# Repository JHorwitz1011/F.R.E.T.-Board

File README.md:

# F.R.E.T.-Board

## Fall '23 Senior Project

Jim Horwitz, Julia Brubach, Peter Buglewicz

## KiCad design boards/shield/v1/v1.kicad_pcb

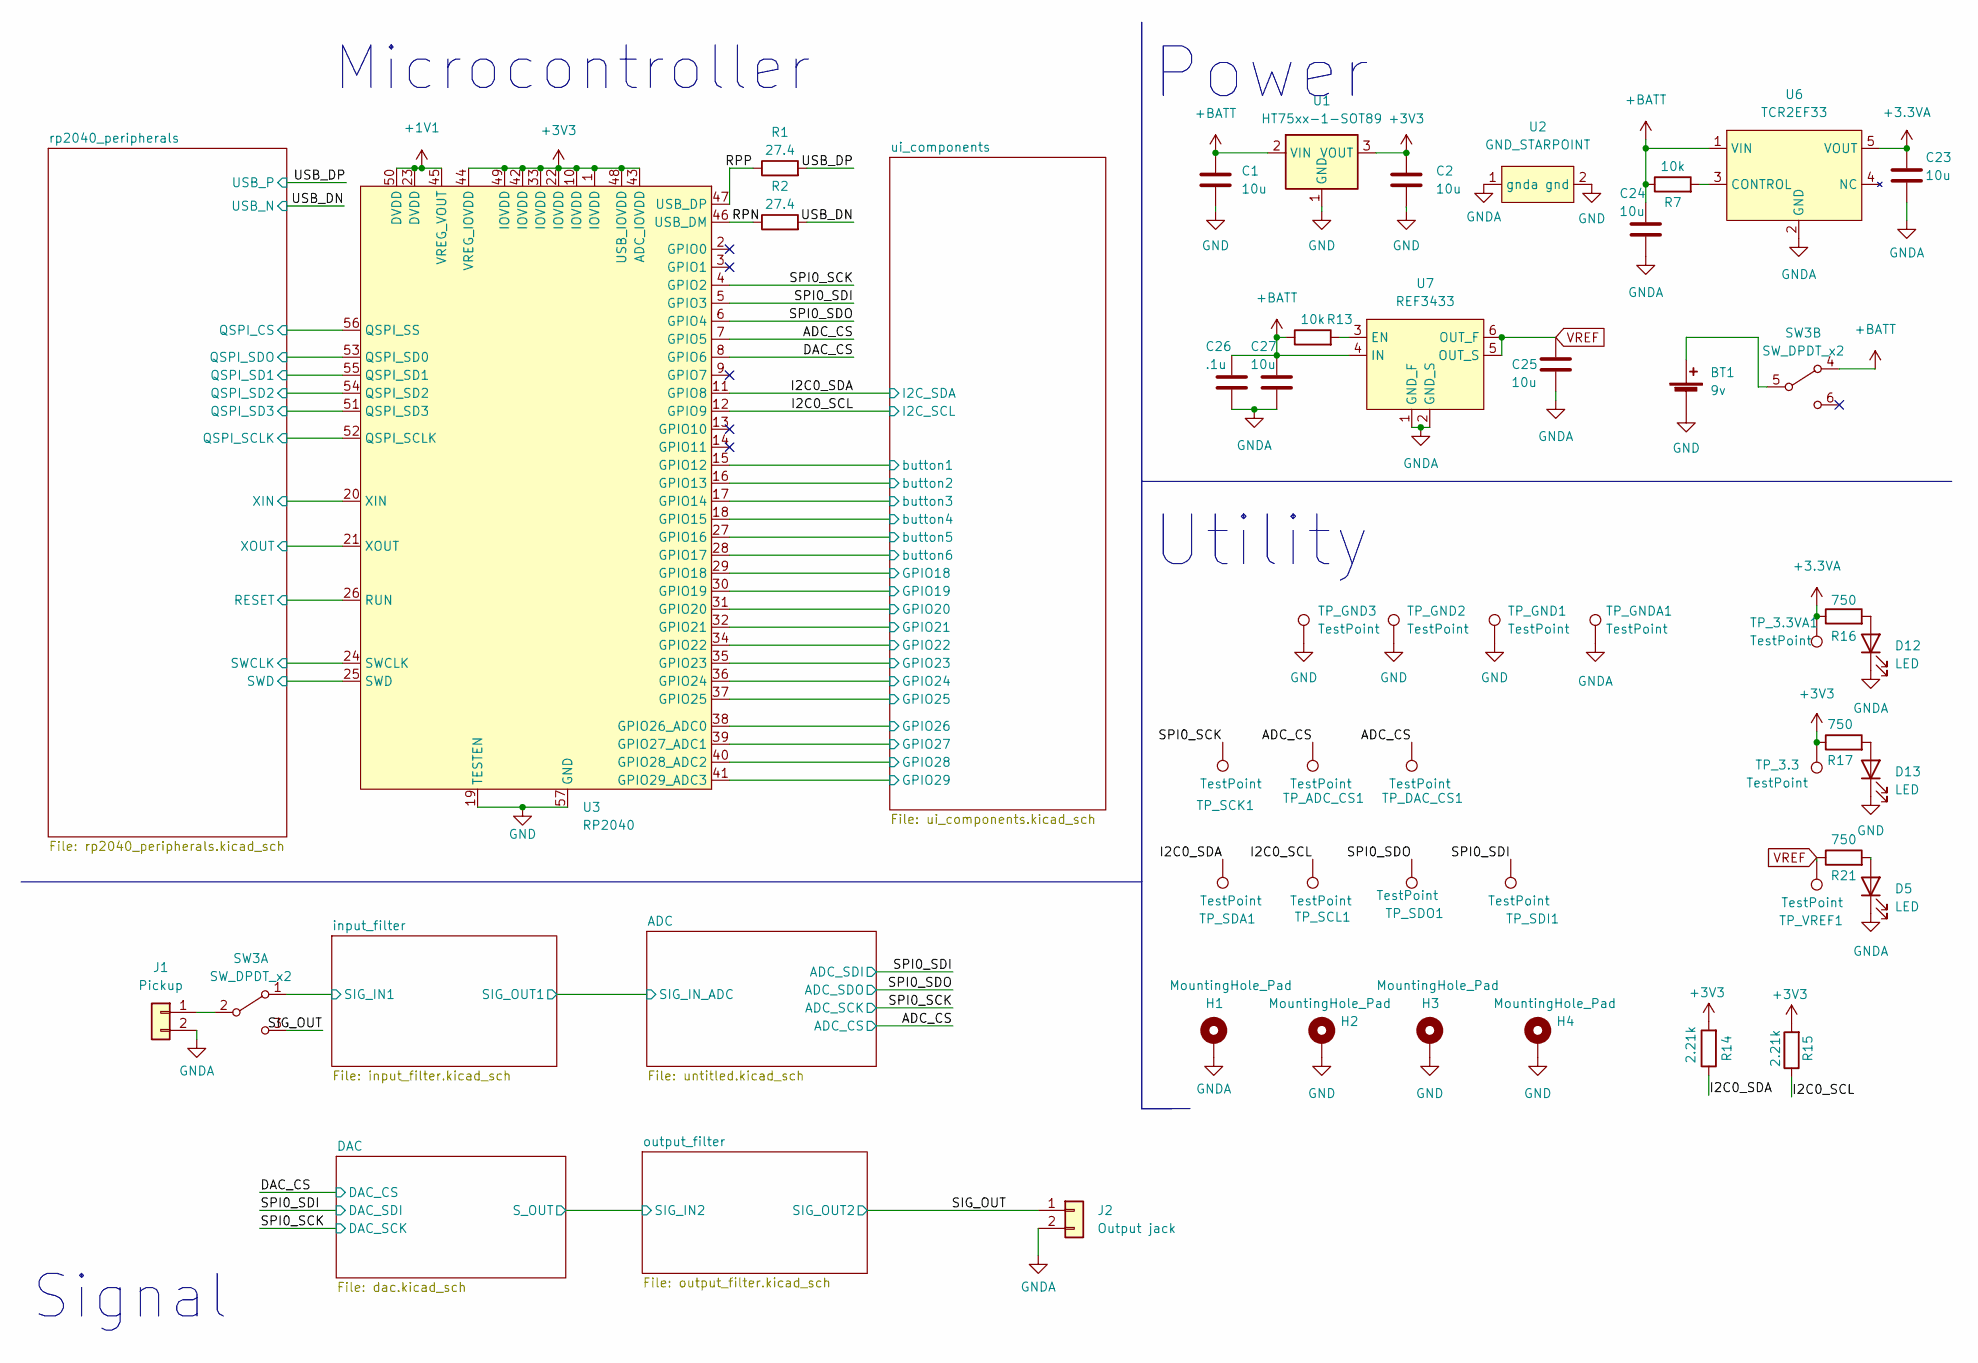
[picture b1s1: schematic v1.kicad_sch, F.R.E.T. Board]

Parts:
BT1: 9v; PinHeader_1x02_P2.54mm_Vertical
C1, C2, C23, C24, C25, C27: 10u; C_0603_1608Metric
C26: .1u; C_0603_1608Metric
D5, D12, D13: LED; LED_0603_1608Metric
H1, H2, H3, H4: MountingHole_Pad; MountingHole_2.2mm_M2_Pad
J1: Pickup; PinHeader_1x02_P2.54mm_Vertical
J2: Output jack; PinHeader_1x02_P2.54mm_Vertical
R1, R2: 27.4; R_0603_1608Metric
R7, R13: 10k; R_0603_1608Metric
R14, R15: 2.21k; R_0603_1608Metric
R16, R17, R21: 750; R_0603_1608Metric
SW3: SW_DPDT_x2; SW_CuK_JS202011CQN_DPDT_Straight
TP_3.3, TP_3.3VA1: TestPoint; TestPoint_Pad_D2.0mm
TP_ADC_CS1: TestPoint; TestPoint_Pad_D2.0mm
TP_DAC_CS1: TestPoint; TestPoint_Pad_D2.0mm
TP_GND1, TP_GND2, TP_GND3: TestPoint; TestPoint_Pad_D2.0mm
TP_GNDA1: TestPoint; TestPoint_Pad_D2.0mm
TP_SCK1: TestPoint; TestPoint_Pad_D2.0mm
TP_SCL1: TestPoint; TestPoint_Pad_D2.0mm
TP_SDA1: TestPoint; TestPoint_Pad_D2.0mm
TP_SDI1: TestPoint; TestPoint_Pad_D2.0mm
TP_SDO1: TestPoint; TestPoint_Pad_D2.0mm
TP_VREF1: TestPoint; TestPoint_Pad_D2.0mm
U1: HT75xx-1-SOT89; SOT-89-3; LCSC Part Number C85233
U2: GND_STARPOINT
U3: RP2040; QFN-56_EP_7.75x7.75_Pitch0.4mm; LCSC Part Number C2040
U6: TCR2EF33; SOT-23-5; LCSC Part Number C843273
U7: REF3433; SOT-23-6; LCSC Part Number C882722

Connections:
+1V1: U3.23 (DVDD), U3.45 (VREG_VOUT), U3.50 (DVDD); also elsewhere on the board
+3.3VA: C23.1, R16.1, TP_3.3VA1.1, U6.5 (VOUT); also elsewhere on the board
+BATT: C1.1, C24.1, C26.1, C27.1, R7.1, R13.1, SW3.4 (A), U1.2 (VIN), U6.1 (VIN), U7.4 (IN)
/ADC_CS: TP_ADC_CS1.1, TP_DAC_CS1.1, U3.7 (GPIO5); also elsewhere on the board
/DAC_CS: U3.8 (GPIO6); also elsewhere on the board
/I2C0_SCL: R15.1, TP_SCL1.1, U3.12 (GPIO9); also elsewhere on the board
/I2C0_SDA: R14.1, TP_SDA1.1, U3.11 (GPIO8); also elsewhere on the board
/RPN: R2.1, U3.46 (USB_DM)
/RPP: R1.1, U3.47 (USB_DP)
/SIG_OUT: J2.1, SW3.3 (C); also elsewhere on the board
/SPI0_SCK: TP_SCK1.1, U3.4 (GPIO2); also elsewhere on the board
/SPI0_SDI: TP_SDI1.1, U3.5 (GPIO3); also elsewhere on the board
/SPI0_SDO: TP_SDO1.1, U3.6 (GPIO4); also elsewhere on the board
/USB_DN: R2.2; also elsewhere on the board
/USB_DP: R1.2; also elsewhere on the board
/input_filter/SIG_IN1: SW3.1 (A); also elsewhere on the board
/rp2040_peripherals/QSPI_CS: U3.56 (QSPI_SS); also elsewhere on the board
/rp2040_peripherals/QSPI_SCLK: U3.52 (QSPI_SCLK); also elsewhere on the board
/rp2040_peripherals/QSPI_SD1: U3.55 (QSPI_SD1); also elsewhere on the board
/rp2040_peripherals/QSPI_SD2: U3.54 (QSPI_SD2); also elsewhere on the board
/rp2040_peripherals/QSPI_SD3: U3.51 (QSPI_SD3); also elsewhere on the board
/rp2040_peripherals/QSPI_SDO: U3.53 (QSPI_SD0); also elsewhere on the board
/rp2040_peripherals/RESET: U3.26 (RUN); also elsewhere on the board
/rp2040_peripherals/SWCLK: U3.24 (SWCLK); also elsewhere on the board
/rp2040_peripherals/SWD: U3.25 (SWD); also elsewhere on the board
/rp2040_peripherals/XIN: U3.20 (XIN); also elsewhere on the board
/rp2040_peripherals/XOUT: U3.21 (XOUT); also elsewhere on the board
/ui_components/GPIO18: U3.29 (GPIO18); also elsewhere on the board
/ui_components/GPIO19: U3.30 (GPIO19); also elsewhere on the board
/ui_components/GPIO20: U3.31 (GPIO20); also elsewhere on the board
/ui_components/GPIO21: U3.32 (GPIO21); also elsewhere on the board
/ui_components/GPIO22: U3.34 (GPIO22); also elsewhere on the board
/ui_components/GPIO23: U3.35 (GPIO23); also elsewhere on the board
/ui_components/GPIO24: U3.36 (GPIO24); also elsewhere on the board
/ui_components/GPIO25: U3.37 (GPIO25); also elsewhere on the board
/ui_components/GPIO26: U3.38 (GPIO26_ADC0); also elsewhere on the board
/ui_components/GPIO27: U3.39 (GPIO27_ADC1); also elsewhere on the board
/ui_components/GPIO28: U3.40 (GPIO28_ADC2); also elsewhere on the board
/ui_components/GPIO29: U3.41 (GPIO29_ADC3); also elsewhere on the board
/ui_components/button1: U3.15 (GPIO12); also elsewhere on the board
/ui_components/button2: U3.16 (GPIO13); also elsewhere on the board
/ui_components/button3: U3.17 (GPIO14); also elsewhere on the board
/ui_components/button4: U3.18 (GPIO15); also elsewhere on the board
/ui_components/button5: U3.27 (GPIO16); also elsewhere on the board
/ui_components/button6: U3.28 (GPIO17); also elsewhere on the board
GND: BT1.2 (-), C1.2, C2.2, D13.1 (K), H2.1, H3.1, H4.1, TP_GND1.1, TP_GND2.1, TP_GND3.1, U1.1 (GND), U2.2 (gnd), U3.19 (TESTEN), U3.57 (GND); also elsewhere on the board
GNDA: C23.2, C24.2, C25.2, C26.2, C27.2, D5.1 (K), D12.1 (K), H1.1, J1.2, J2.2, TP_GNDA1.1, U2.1 (gnda), U6.2 (GND), U7.1 (GND_F), U7.2 (GND_S); also elsewhere on the board
unnamed: BT1.1 (+), SW3.5 (B)
unnamed: D5.2 (A), R21.2
unnamed: D12.2 (A), R16.2
unnamed: D13.2 (A), R17.2
unnamed: J1.1, SW3.2 (B)
unnamed: R7.2, U6.3 (CONTROL)
unnamed: R13.2, U7.3 (EN)
VREF: C25.1, R21.1, TP_VREF1.1, U7.5 (OUT_S), U7.6 (OUT_F); also elsewhere on the board

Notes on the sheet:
Microcontroller
Signal
Power
Utility

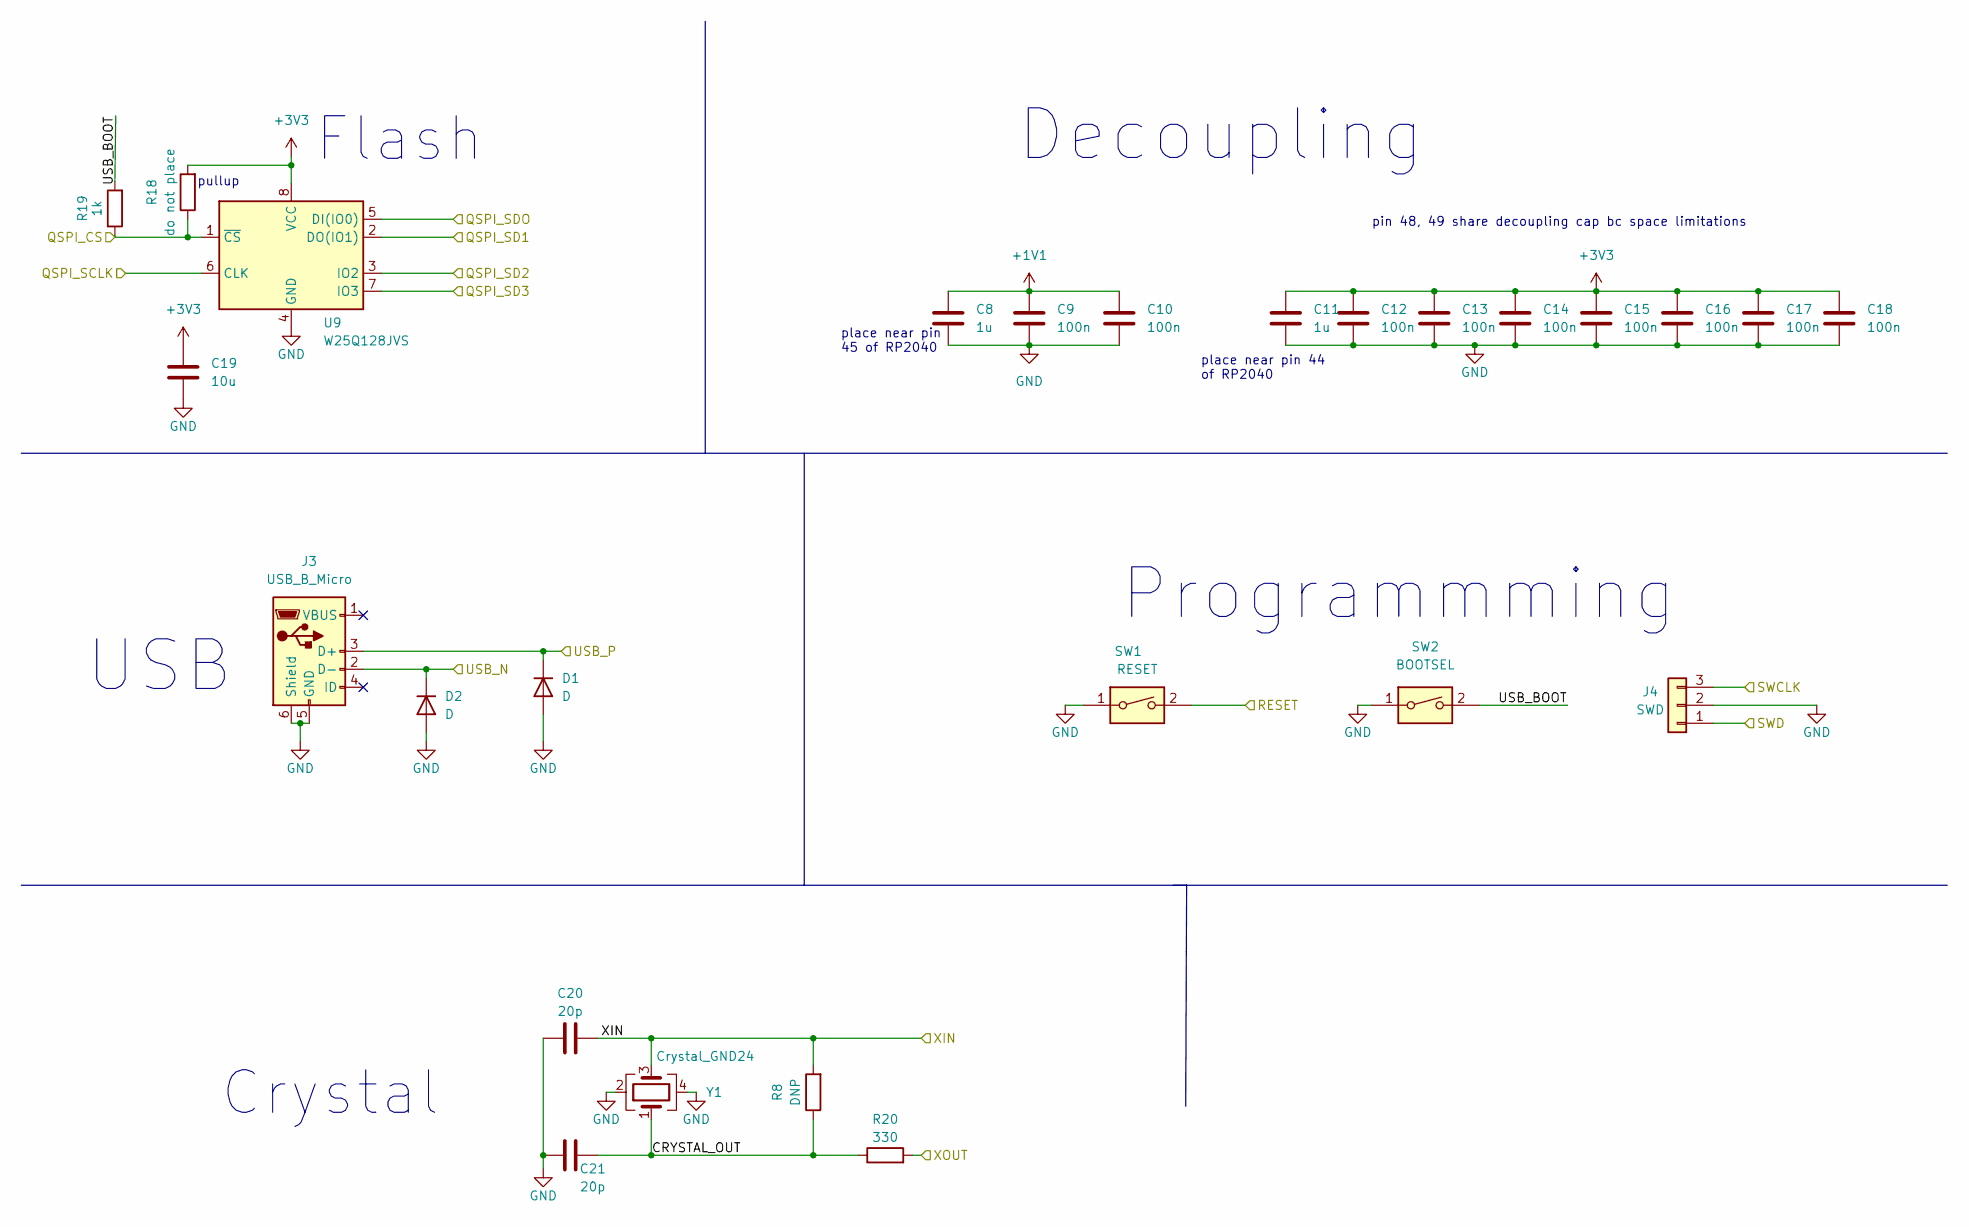
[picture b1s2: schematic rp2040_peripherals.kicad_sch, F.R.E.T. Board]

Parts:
C8, C11: 1u; C_0603_1608Metric
C9, C10, C12, C13, C14, C15, C16, C17, C18: 100n; C_0603_1608Metric
C19: 10u; C_0603_1608Metric
C20, C21: 20p; C_0603_1608Metric
D1, D2: D; D_0603_1608Metric
J3: USB_B_Micro; U254-051T-4BH83-S1S; LCSC Part Number C319160
J4: SWD; PinHeader_1x03_P2.54mm_Vertical
R8: DNP; R_0603_1608Metric
R18: do not place; R_0603_1608Metric
R19: 1k; R_0603_1608Metric
R20: 330; R_0603_1608Metric
SW1: RESET; PTS636 6.0x3.5 Button; LCSC Part Number C2800965
SW2: BOOTSEL; PTS636 6.0x3.5 Button; LCSC Part Number C2800965
U9: W25Q128JVS; SOIC-8_5.23x5.23mm_P1.27mm; LCSC Part Number C97521
Y1: Crystal_GND24; Crystal_SMD_2520-4Pin_2.5x2.0mm; LCSC Part Number C2686253

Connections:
+1V1: C8.1, C9.1, C10.1; also elsewhere on the board
/USB_DN: D2.1 (K), J3.2 (D-); also elsewhere on the board
/USB_DP: D1.1 (K), J3.3 (D+); also elsewhere on the board
/rp2040_peripherals/CRYSTAL_OUT: C21.1, R8.1, R20.1, Y1.1
/rp2040_peripherals/QSPI_CS: R18.1, R19.1, U9.1 (~CS); also elsewhere on the board
/rp2040_peripherals/QSPI_SCLK: U9.6 (CLK); also elsewhere on the board
/rp2040_peripherals/QSPI_SD1: U9.2 (DO(IO1)); also elsewhere on the board
/rp2040_peripherals/QSPI_SD2: U9.3 (IO2); also elsewhere on the board
/rp2040_peripherals/QSPI_SD3: U9.7 (IO3); also elsewhere on the board
/rp2040_peripherals/QSPI_SDO: U9.5 (DI(IO0)); also elsewhere on the board
/rp2040_peripherals/RESET: SW1.2; also elsewhere on the board
/rp2040_peripherals/SWCLK: J4.3; also elsewhere on the board
/rp2040_peripherals/SWD: J4.1; also elsewhere on the board
/rp2040_peripherals/USB_BOOT: R19.2, SW2.2
/rp2040_peripherals/XIN: C20.1, R8.2, Y1.3; also elsewhere on the board
/rp2040_peripherals/XOUT: R20.2; also elsewhere on the board
GND: C8.2, C9.2, C10.2, C11.2, C12.2, C13.2, C14.2, C15.2, C16.2, C17.2, C18.2, C19.2, C20.2, C21.2, D1.2 (A), D2.2 (A), J3.5 (GND), J3.6 (Shield), J4.2, SW1.1, SW2.1, U9.4 (GND), Y1.2, Y1.4; also elsewhere on the board

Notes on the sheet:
pullup
Flash
Crystal
place near pin 44 of RP2040
USB
Decoupling
place near pin 45 of RP2040
pin 48, 49 share decoupling cap bc space limitations
Programmming

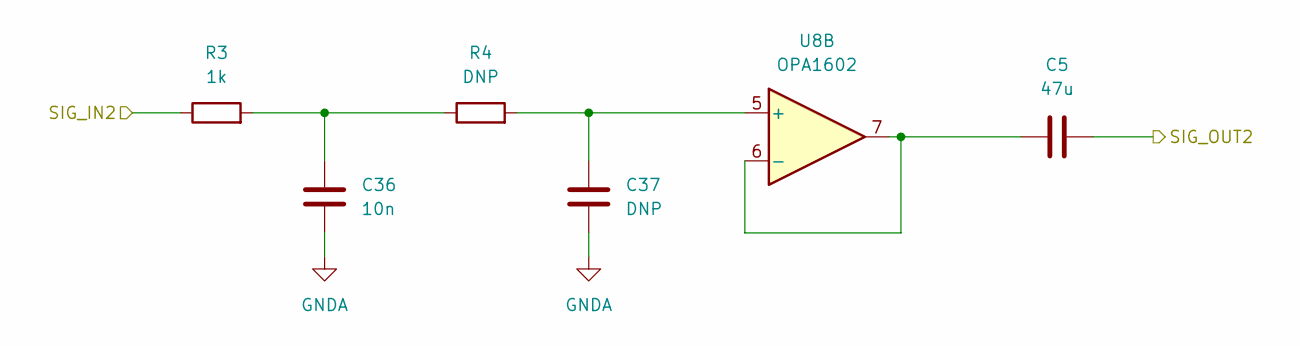
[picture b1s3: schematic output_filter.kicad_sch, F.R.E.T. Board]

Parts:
C5: 47u; C_1210_3225Metric
C36: 10n; C_0603_1608Metric
C37: DNP; C_0603_1608Metric
R3: 1k; R_0603_1608Metric
R4: DNP; R_0603_1608Metric
U8: OPA1602; OPA1602AIDR

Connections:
/DAC/S_OUT: R3.1; also elsewhere on the board
/SIG_OUT: C5.2; also elsewhere on the board
GNDA: C36.2, C37.2; also elsewhere on the board
unnamed: C5.1, U8.6 (-), U8.7
unnamed: C36.1, R3.2, R4.1
unnamed: C37.1, R4.2, U8.5 (+)

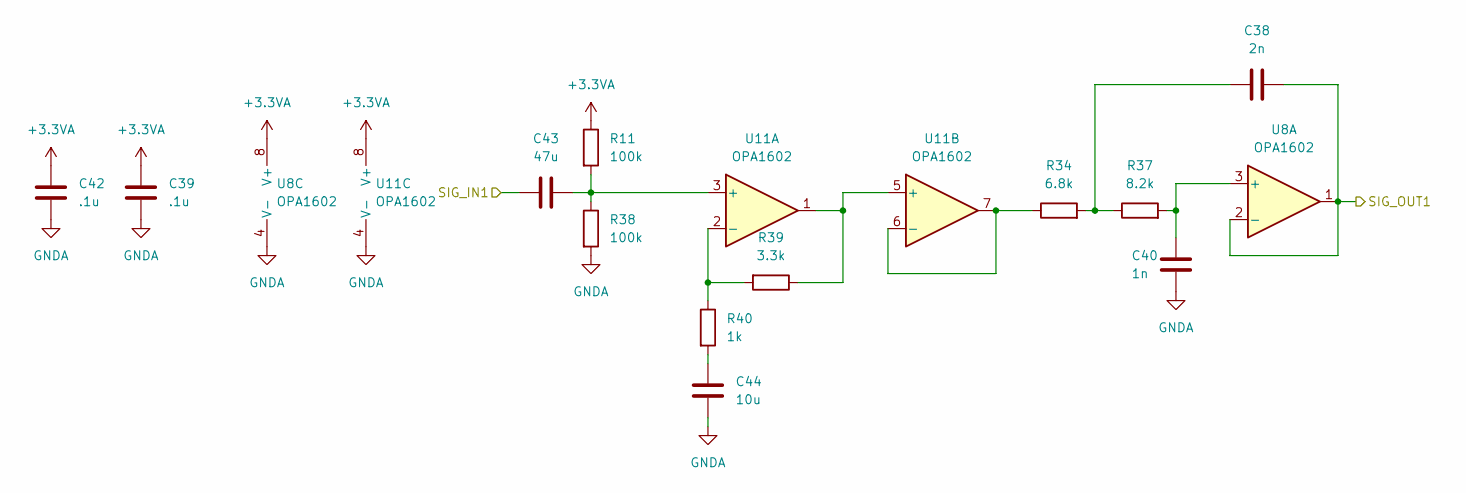
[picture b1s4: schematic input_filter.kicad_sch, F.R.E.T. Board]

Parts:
C38: 2n; C_0603_1608Metric
C39, C42: .1u; C_0603_1608Metric
C40: 1n; C_0603_1608Metric
C43: 47u; C_1210_3225Metric
C44: 10u; C_0603_1608Metric
R11, R38: 100k; R_0603_1608Metric
R34: 6.8k; R_0603_1608Metric
R37: 8.2k; R_0603_1608Metric
R39: 3.3k; R_0603_1608Metric
R40: 1k; R_0603_1608Metric
U8, U11: OPA1602; OPA1602AIDR

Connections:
+3.3VA: C39.1, C42.1, R11.1, U8.8 (V+), U11.8 (V+); also elsewhere on the board
/ADC/SIG_IN_ADC: C38.2, U8.1, U8.2 (-); also elsewhere on the board
/input_filter/SIG_IN1: C43.1; also elsewhere on the board
GNDA: C39.2, C40.1, C42.2, C44.1, R38.2, U8.4 (V-), U11.4 (V-); also elsewhere on the board
unnamed: C38.1, R34.2, R37.1
unnamed: C40.2, R37.2, U8.3 (+)
unnamed: C43.2, R11.2, R38.1, U11.3 (+)
unnamed: C44.2, R40.2
unnamed: R34.1, U11.6 (-), U11.7
unnamed: R39.1, U11.1, U11.5 (+)
unnamed: R39.2, R40.1, U11.2 (-)

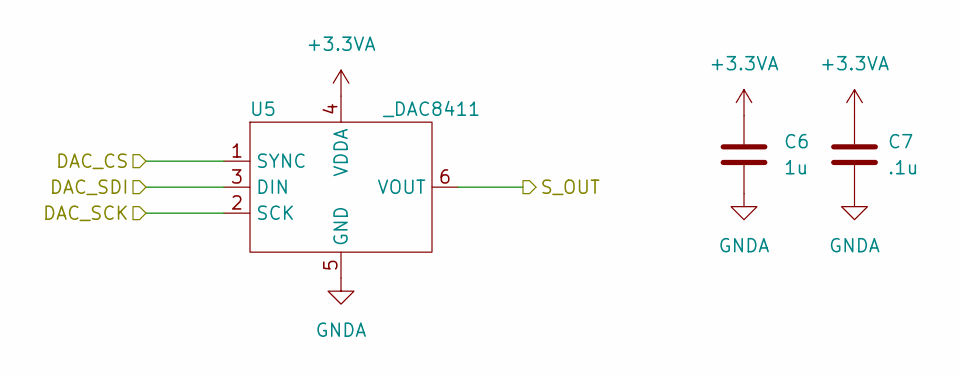
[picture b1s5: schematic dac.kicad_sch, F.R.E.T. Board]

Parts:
C6: 1u; C_0603_1608Metric
C7: .1u; C_0603_1608Metric
U5: _DAC8411; Texas_R-PDSO-G6; LCSC Part Number C2926925

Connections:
+3.3VA: C6.1, C7.1, U5.4 (VDDA); also elsewhere on the board
/DAC/S_OUT: U5.6 (VOUT); also elsewhere on the board
/DAC_CS: U5.1 (SYNC); also elsewhere on the board
/SPI0_SCK: U5.2 (SCK); also elsewhere on the board
/SPI0_SDI: U5.3 (DIN); also elsewhere on the board
GNDA: C6.2, C7.2, U5.5 (GND); also elsewhere on the board

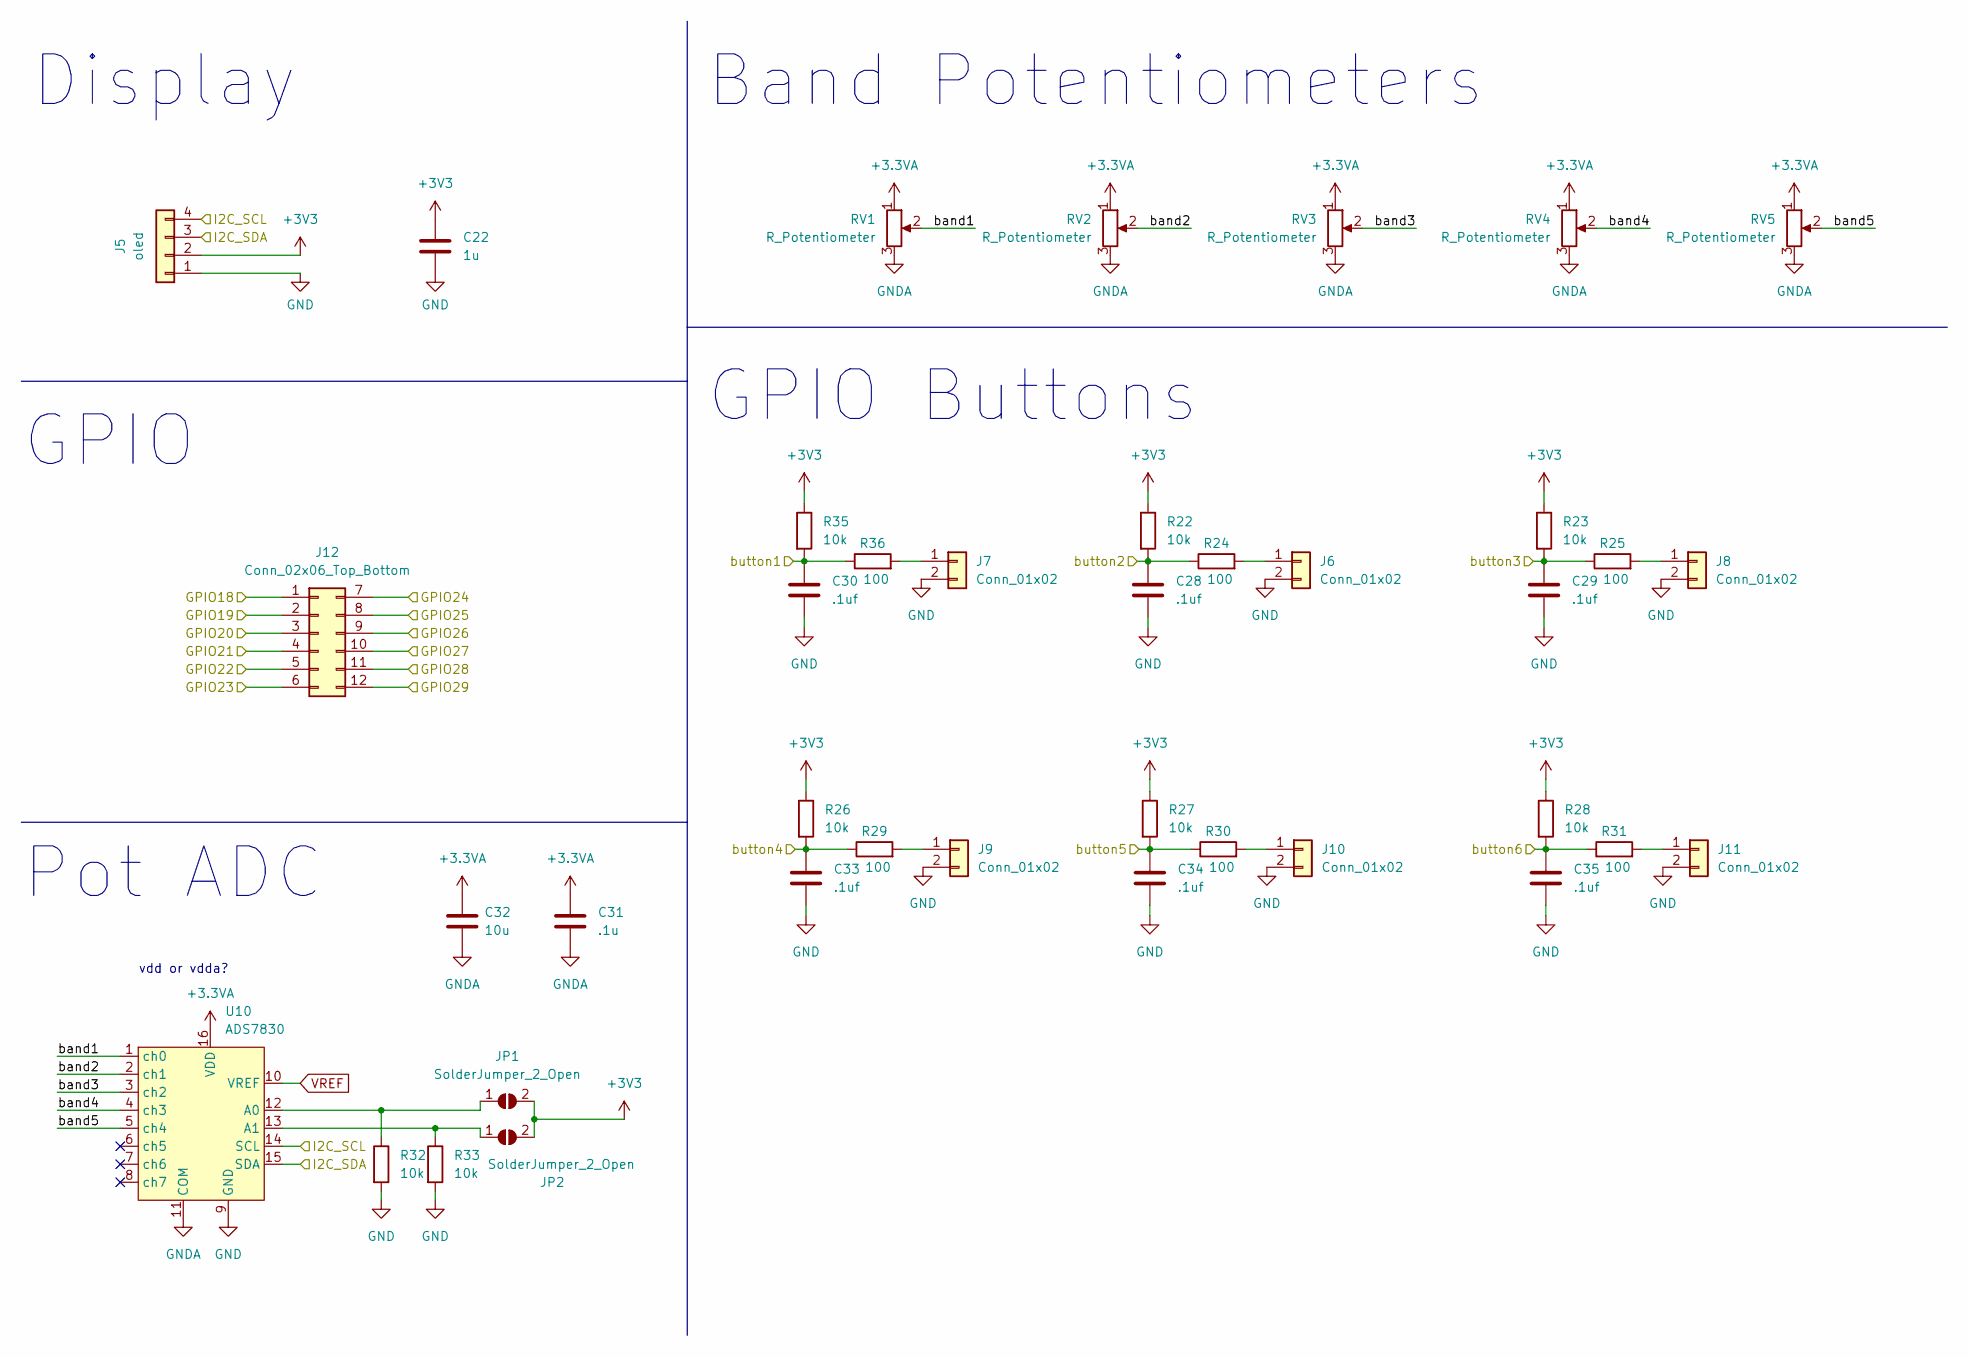
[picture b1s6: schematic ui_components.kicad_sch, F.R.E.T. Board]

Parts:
C22: 1u; C_0603_1608Metric
C28, C29, C30, C33, C34, C35: .1uf; C_0603_1608Metric
C31: .1u; C_0603_1608Metric
C32: 10u; C_0603_1608Metric
J5: oled; PinHeader_1x04_P2.54mm_Vertical
J6, J7, J8, J9, J10, J11: Conn_01x02; PinHeader_1x02_P2.54mm_Vertical
J12: Conn_02x06_Top_Bottom; PinHeader_2x06_P2.54mm_Vertical
JP1, JP2: SolderJumper_2_Open; SolderJumper-2_P1.3mm_Open_TrianglePad1.0x1.5mm
R22, R23, R26, R27, R28, R32, R33, R35: 10k; R_0603_1608Metric
R24, R25, R29, R30, R31, R36: 100; R_0603_1608Metric
RV1, RV2, RV3, RV4, RV5: R_Potentiometer; PS30-10PB1BR10K
U10: ADS7830; PW16; LCSC Part Number C161747

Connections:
+3.3VA: C31.1, C32.1, RV1.1, RV2.1, RV3.1, RV4.1, RV5.1, U10.16 (VDD); also elsewhere on the board
/I2C0_SCL: J5.4, U10.14 (SCL); also elsewhere on the board
/I2C0_SDA: J5.3, U10.15 (SDA); also elsewhere on the board
/ui_components/GPIO18: J12.1; also elsewhere on the board
/ui_components/GPIO19: J12.2; also elsewhere on the board
/ui_components/GPIO20: J12.3; also elsewhere on the board
/ui_components/GPIO21: J12.4; also elsewhere on the board
/ui_components/GPIO22: J12.5; also elsewhere on the board
/ui_components/GPIO23: J12.6; also elsewhere on the board
/ui_components/GPIO24: J12.7; also elsewhere on the board
/ui_components/GPIO25: J12.8; also elsewhere on the board
/ui_components/GPIO26: J12.9; also elsewhere on the board
/ui_components/GPIO27: J12.10; also elsewhere on the board
/ui_components/GPIO28: J12.11; also elsewhere on the board
/ui_components/GPIO29: J12.12; also elsewhere on the board
/ui_components/band1: RV1.2, U10.1 (ch0)
/ui_components/band2: RV2.2, U10.2 (ch1)
/ui_components/band3: RV3.2, U10.3 (ch2)
/ui_components/band4: RV4.2, U10.4 (ch3)
/ui_components/band5: RV5.2, U10.5 (ch4)
/ui_components/button1: C30.1, R35.2, R36.1; also elsewhere on the board
/ui_components/button2: C28.1, R22.2, R24.1; also elsewhere on the board
/ui_components/button3: C29.1, R23.2, R25.1; also elsewhere on the board
/ui_components/button4: C33.1, R26.2, R29.1; also elsewhere on the board
/ui_components/button5: C34.1, R27.2, R30.1; also elsewhere on the board
/ui_components/button6: C35.1, R28.2, R31.1; also elsewhere on the board
GND: C22.2, C28.2, C29.2, C30.2, C33.2, C34.2, C35.2, J5.1, J6.2, J7.2, J8.2, J9.2, J10.2, J11.2, R32.2, R33.2, U10.9 (GND); also elsewhere on the board
GNDA: C31.2, C32.2, RV1.3, RV2.3, RV3.3, RV4.3, RV5.3, U10.11 (COM); also elsewhere on the board
unnamed: J6.1, R24.2
unnamed: J7.1, R36.2
unnamed: J8.1, R25.2
unnamed: J9.1, R29.2
unnamed: J10.1, R30.2
unnamed: J11.1, R31.2
unnamed: JP1.1 (A), R32.1, U10.12 (A0)
unnamed: JP2.1 (A), R33.1, U10.13 (A1)
VREF: U10.10 (VREF); also elsewhere on the board

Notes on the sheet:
vdd or vdda?
Display
GPIO
Band Potentiometers
Pot ADC
GPIO Buttons

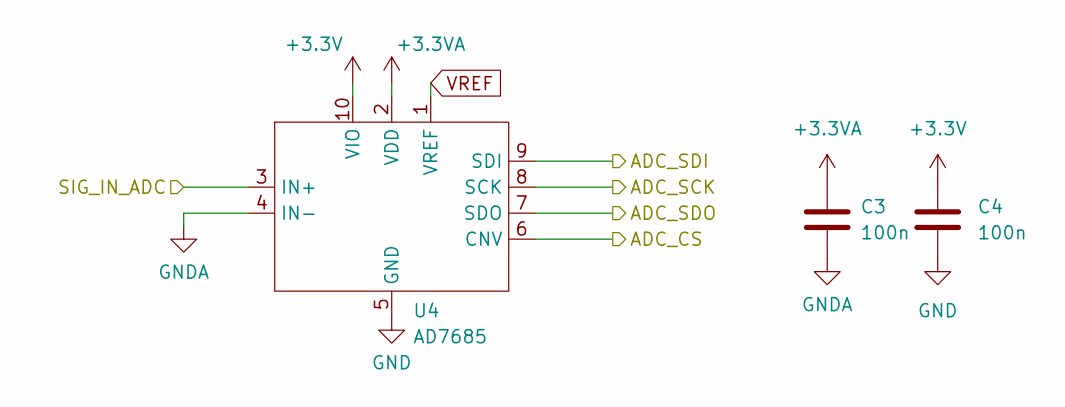
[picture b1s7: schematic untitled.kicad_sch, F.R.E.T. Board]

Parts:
C3, C4: 100n; C_0603_1608Metric
U4: AD7685; MSOP-10_3x3mm_P0.5mm; LCSC Part Number C44637

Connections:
+3.3VA: C3.1, U4.2 (VDD); also elsewhere on the board
/ADC/SIG_IN_ADC: U4.3 (IN+); also elsewhere on the board
/ADC_CS: U4.6 (CNV); also elsewhere on the board
/SPI0_SCK: U4.8 (SCK); also elsewhere on the board
/SPI0_SDI: U4.9 (SDI); also elsewhere on the board
/SPI0_SDO: U4.7 (SDO); also elsewhere on the board
GND: C4.2, U4.5 (GND); also elsewhere on the board
GNDA: C3.2, U4.4 (IN-); also elsewhere on the board
VREF: U4.1 (VREF); also elsewhere on the board

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
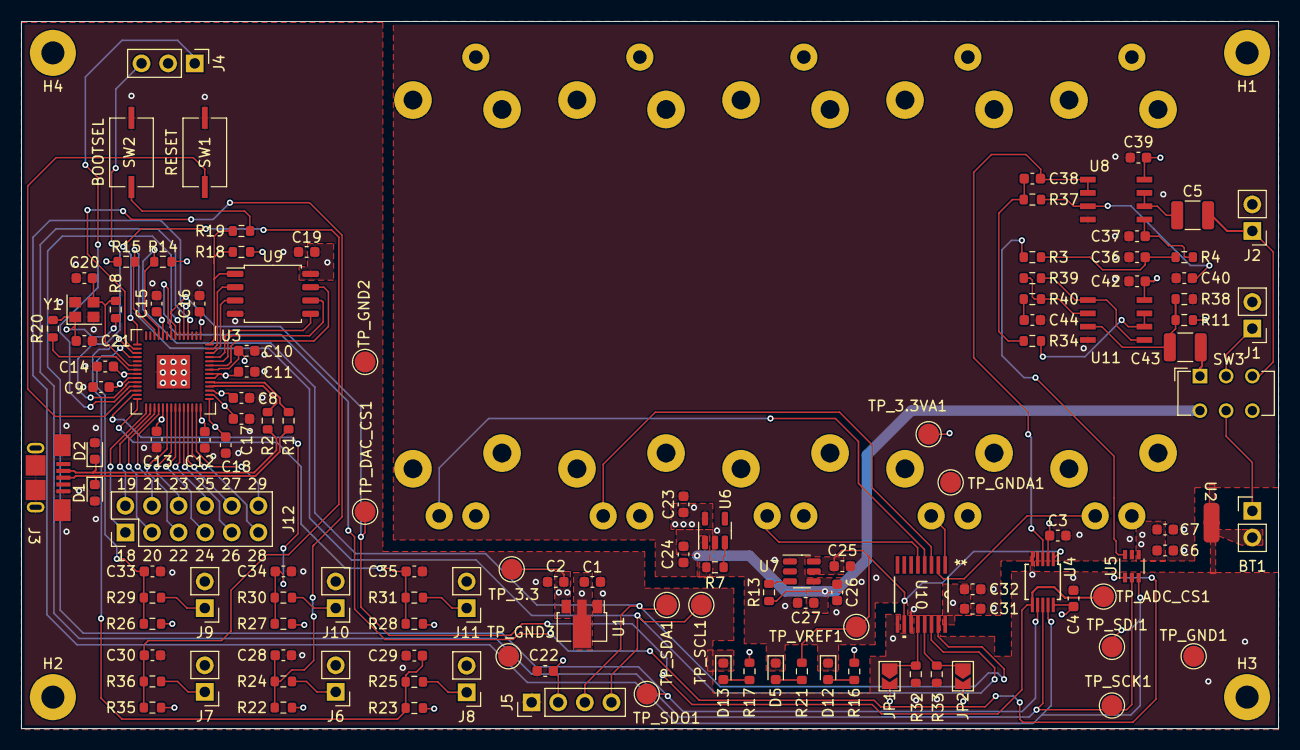
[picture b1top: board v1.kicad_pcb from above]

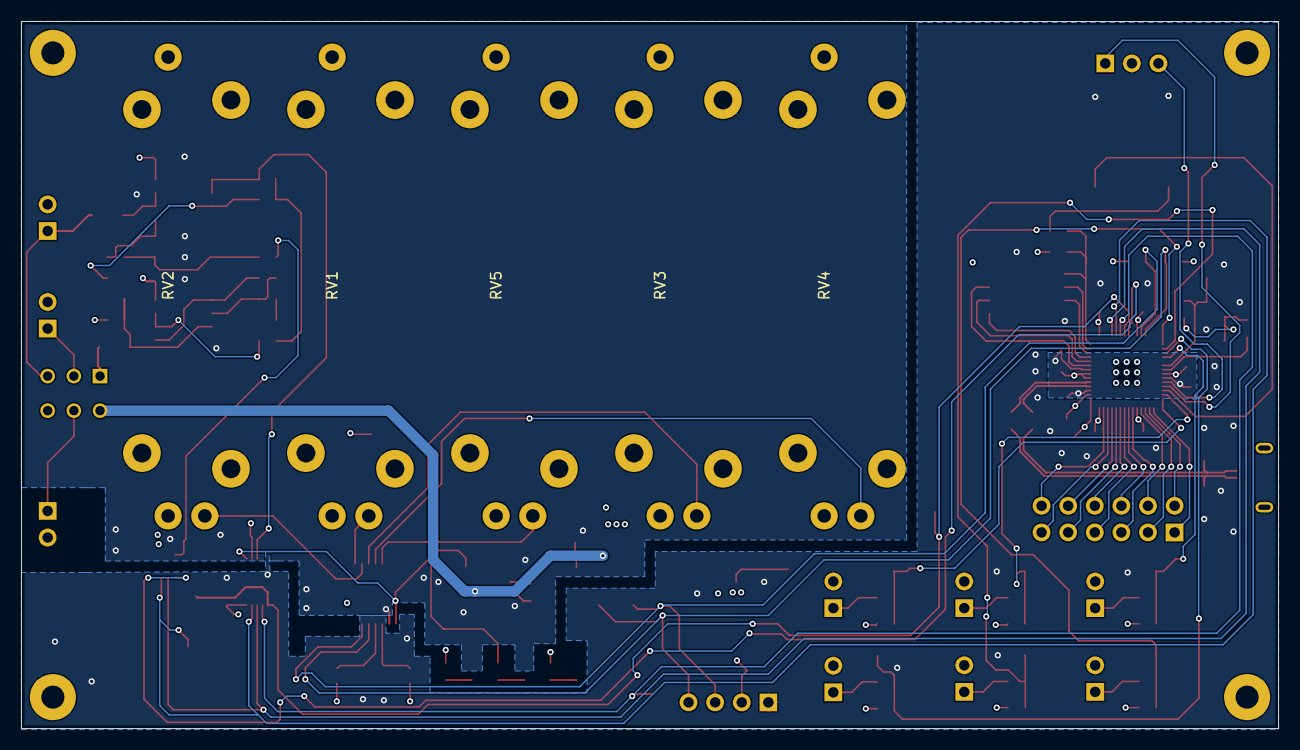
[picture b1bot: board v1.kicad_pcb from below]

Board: 4 copper layers, 120.0 x 67.5 mm, 136 parts (5 on the bottom side), 83 nets.

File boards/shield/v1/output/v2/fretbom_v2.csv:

Comment,Designator,Footprint,LCSC Part #
10u Unpolarized capacitor,"C1,C2,C19,C23,C24,C25,C27,C32,C44",C_0603_1608Metric,
100n Unpolarized capacitor,"C3,C4,C9,C10,C12,C13,C14,C15,C16,C17,C18",C_0603_1608Metric,
47u Unpolarized capacitor,"C5,C43",C_1210_3225Metric,C778723
1u Unpolarized capacitor,"C6,C8,C11,C22",C_0603_1608Metric,
.1u Unpolarized capacitor,"C7,C26,C31,C39,C42",C_0603_1608Metric,
20p Unpolarized capacitor,"C20,C21",C_0603_1608Metric,
.1uf Unpolarized capacitor,"C28,C29,C30,C33,C34,C35",C_0603_1608Metric,
10nF Unpolarized capacitor,C36,C_0603_1608Metric,
2n Unpolarized capacitor,C38,C_0603_1608Metric,
1n Unpolarized capacitor,C40,C_0603_1608Metric,
LED Light emitting diode,"D5,D12,D13",LED_0603_1608Metric,C241893
USB_B_Micro USB Micro Type B connector,J3,U254-051T-4BH83-S1S,C319160
27.4 Resistor,"R1,R2",R_0603_1608Metric,
1k Resistor,"R3,R19,R40",R_0603_1608Metric,
10k Resistor,"R7,R13,R22,R23,R26,R27,R28,R32,R33,R35",R_0603_1608Metric,
100k Resistor,"R11,R38",R_0603_1608Metric,
2.21k Resistor,"R14,R15",R_0603_1608Metric,
750 Resistor,"R16,R17,R21",R_0603_1608Metric,
330 Resistor,R20,R_0603_1608Metric,
100 Resistor,"R24,R25,R29,R30,R31,R36",R_0603_1608Metric,
6.34k Resistor,R34,R_0603_1608Metric,
8.66k Resistor,R37,R_0603_1608Metric,
3.3k Resistor,R39,R_0603_1608Metric,
"RESET 1x DIP Switch, Single Pole Single Throw (SPST) switch, small symbol",SW1,PTS636 6.0x3.5 Button,C2800965
"BOOTSEL 1x DIP Switch, Single Pole Single Throw (SPST) switch, small symbol",SW2,PTS636 6.0x3.5 Button,C2800965
ME6210A33PG,U1,SOT-89-3,C85233
RP2040,U3,QFN-56_EP_7.75x7.75_Pitch0.4mm,C2040
AD7685,U4,MSOP-10_3x3mm_P0.5mm,C161747
_DAC8411,U5,Texas_R-PDSO-G6,C2926925
TCR2EF33,U6,SOT-23-5,C843273
REF3433,U7,SOT-23-6,C882722
"OPA1602 Dual SoundPlus High Performance, Bipolar-Input Audio Operational Amplifiers, SOIC-8/MSOP-8","U8,U11",MSOP-8_3x3mm_P0.65mm,C70884
"W25Q128JVS 128Mb Serial Flash Memory, Standard/Dual/Quad SPI, SOIC-8",U9,SOIC-8_5.23x5.23mm_P1.27mm,C2613930
ADS7830,U10,TSSOP-16_4.4x5mm_P0.65mm,C161747
"Crystal_GND24 Four pin crystal, GND on pins 2 and 4",Y1,Crystal_SMD_2520-4Pin_2.5x2.0mm,C2686253

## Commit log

2023-10-06 board done;
2023-10-24 code folder
2023-10-24 code added
2023-10-31 dac and adc examples written
2023-11-17 adding code
2023-11-17 gitignore build repo
2023-11-17 removed vsc
2023-11-17 testing gitignore
2023-11-17 gitignore testing
2023-11-17 added folder for julia, added zach stuff
2023-11-17 worked on architecture and filtering
2023-11-17 filtering work
2023-11-17 architecture work
2023-11-17 updated filtering
2023-11-18 best practices stuff
2023-11-18 i2c adc pushed
2023-11-24 reworking fixed point filtering. see examples/filtering
2023-11-24 fixed point testing
2023-11-24 uint to fixed and fixed to uint work. all thats left is to test multiply functionality
2023-11-26 filters testing rig setup
2023-11-26 testing rig setup for filters
2023-11-26 filter test rig
2023-11-27 main created
2023-11-28 updated highpass coeffs
2023-11-28 fixed negative
2023-11-29 coefficients yay
2023-11-29 graphs
2023-11-29 filtering work again
2023-12-03 AHHHHHHHHHH (filtering works fixed indice errors
2023-12-03 pus hfor peter
2023-12-03 refactored filters
2023-12-03 rewrote cmake to export main.c
2023-12-03 fixed
2023-12-03 fixed multicore linkererror
2023-12-06 filtering function succesfully mixing with gains
2023-12-06 sfint dac and adc works
2023-12-06 i2c sliders work
2023-12-07 singlecore works
2023-12-07 release works!
